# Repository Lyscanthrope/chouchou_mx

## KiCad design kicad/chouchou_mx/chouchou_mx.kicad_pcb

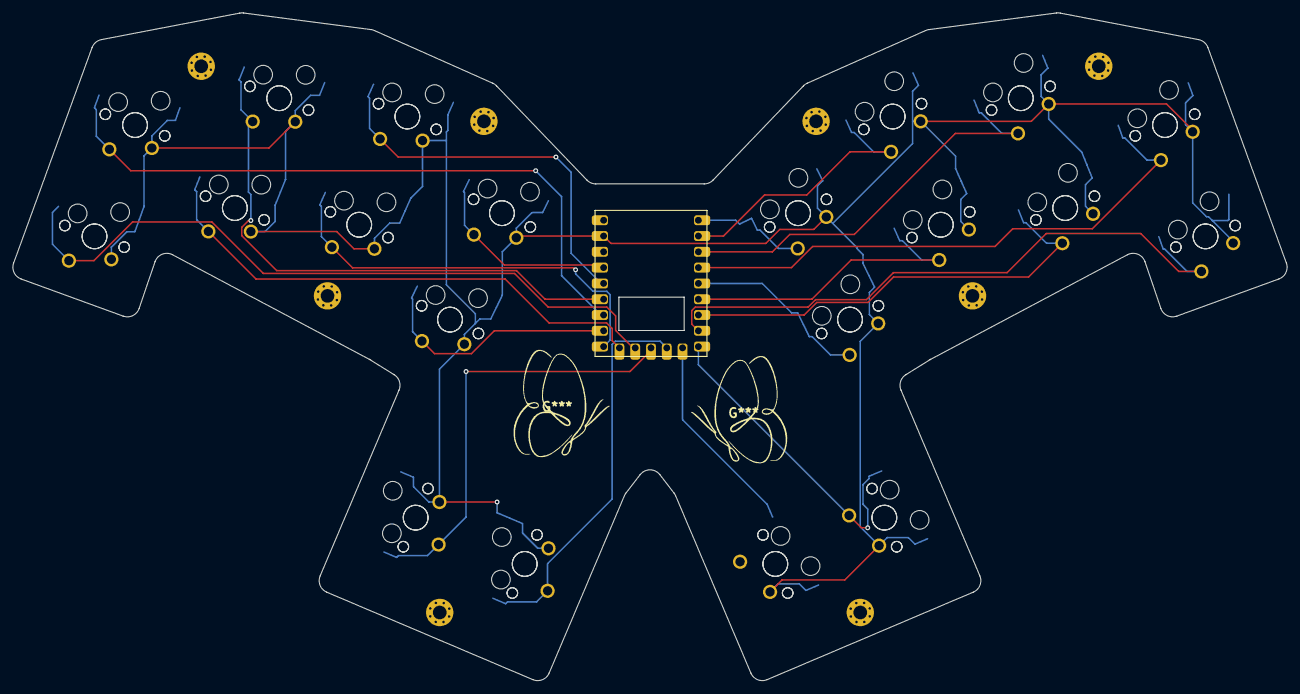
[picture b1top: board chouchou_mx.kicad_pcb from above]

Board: 2 copper layers, 204.9 x 107.4 mm, 49 parts (0 on the bottom side), 21 nets.

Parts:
RP2040Zero1: RP2040-Zero
S1, S2, S3, S4, S5, S6, S7, S8, S9, S10, S11, S12, S13, S14, S15, S16, S17, S18, S19, S20, S21, S22, S23, S24, S25, S26, S27, S28, S29, S30, S31, S32, S33, S34, S35, S36, S37, S38, S39, S40: MX
_1, _2, _3, _4, _5, _6, _7, _8: MountingHole_2.2mm_M2_Pad_Via

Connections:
GND: RP2040Zero1.20, S1.2, S2.2, S3.2, S4.2, S5.2, S6.2, S7.2, S8.2, S9.2, S10.2, S11.2, S12.2, S13.2, S14.2, S15.2, S16.2, S17.2, S18.2, S19.2, S20.2, S21.2, S22.2, S23.2, S24.2, S25.2, S26.2, S27.2, S28.2, S29.2, S30.2, S31.2, S32.2, S33.2, S34.2, S35.2, S36.2, S37.2, S38.2, S39.2, S40.2
GP0: RP2040Zero1.1, S18.1, S38.1
GP1: RP2040Zero1.2, S16.1, S36.1
GP2: RP2040Zero1.3, S14.1, S34.1
GP3: RP2040Zero1.4, S12.1, S32.1
GP4: RP2040Zero1.5, S17.1, S37.1
GP5: RP2040Zero1.6, S15.1, S35.1
GP6: RP2040Zero1.7, S13.1, S33.1
GP7: RP2040Zero1.8, S11.1, S31.1
GP8: RP2040Zero1.9, S19.1, S39.1
GP9: RP2040Zero1.10, S20.1, S40.1
GP10: RP2040Zero1.11, S10.1, S30.1
GP11: RP2040Zero1.12, S9.1, S29.1
GP12: RP2040Zero1.13, S1.1, S21.1
GP13: RP2040Zero1.14, S3.1, S23.1
GP14: RP2040Zero1.15, S5.1, S25.1
GP15: RP2040Zero1.16, S7.1, S27.1
GP26: RP2040Zero1.17, S2.1, S22.1
GP27: RP2040Zero1.18, S4.1, S24.1
GP28: RP2040Zero1.22, S6.1, S26.1
GP29: RP2040Zero1.23, S8.1, S28.1

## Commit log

2025-02-20 first version
2025-02-21 update with thumb closer
2025-02-21 addition of mx pdf
2025-03-24 update on the gerber for minimx and start of code for the french chouchou using kmk
